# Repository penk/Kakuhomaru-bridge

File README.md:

# The Kakuhomaru Bridge Pickup for Electric Violins 

The Kakuhomaru (角宝丸) bridge is a piezoelectric pickup for electric violins, designed with a ‘one-sensor-per-string’ approach to capture each note with clarity and richness.

🔊 Listen to the open string sample here:

https://github.com/penk/Kakuhomaru-bridge/assets/61878/6f59927d-60b6-4801-80bd-5c879a68bae8

## Bill of materials  

Each Kakuhomaru bridge is composed of 4 main parts:

1. Piezoelectric rods and shielded cable (repurposed from guitar undersaddle pickups).
2. 3D printable case (available in both [low profile](./case/kakuhomaru-case-lowp.stl) and [high profile](./case/kakuhomaru-case-highp.stl)).
3. Custom printed circuit board (PCB) with castellated holes.
4. Semi-rigid electronically conductive foam (I'm using [this one](https://www.distrelec.de/en/conductive-foam-305x305x6mm-rnd-rnd-600-00067/p/30130228) which has a `30 ohm-meter (Ω·m)` volume resistance).

While some parts may require a few days of lead time, the assembly is straightforward and DIY-friendly once all components are in hand.

## Ordering the PCB

To get started with your PCB order, upload the [production file](./production/kakuhomaru-bridge-gerbers.zip) to your preferred PCB manufacturer, such as JLCPCB or PCBWay. Ensure you select `Castellated Holes`—essential for the functionality of our bridge pickup.

Here are the specifications I used for our prototype:

```
PCB Thickness: 1.6 mm 
PCB Color: Black
Remove Order Number: Yes
Castellated Holes: Yes
Edges: 2
```

For reference, ordering 10pcs from JLCPCB cost approximately $40. This should help you budget for your build.

## Assembly Instructions 

- Step 1: Attach the Piezoelectric Rods

    Carefully slice open the heat shrink tubing of the under-saddle pickup with a utility knife to retrieve the piezoelectric ceramics. Position the ceramics with the positive end towards the  E string (treble side) and the marked negative end towards the G string (bass side) . Fix them in place on the PCB using a tiny drop of CA glue at each end.

- Step 2: Solder the Shielded Cable & Insert the Conductive Foam

    Strip back a small portion of the shielded cable to expose the central positive wire. Solder this wire to the positive through-hole on the PCB. Attach the braided mesh, which acts as the negative wire, to the `GND` (ground) through-hole. Then, insert conductive foam into the eight castellated holes, using approximately 5mm cubic pieces.

- Step 3: Close the Protective Case  

    Place the PCB assmebly inside the [3D printed case](./case/) and secure it with two M2x10 screws. 

🔊 Test the bridge assembly with an amplifier once you complete the assembly to ensure proper functionality.

https://github.com/penk/Kakuhomaru-bridge/assets/61878/055f79b9-ad49-477b-b956-cf757c91dd27

## Setting up 

- Shielding: There's no need for copper shielding tape due to the PCB's integrated ground plane, which reduces interference.
- Grounding: Establish a grounding connection by connecting the shielded cable to the tuning pegs (if applicable) or directly to the string ends, depending on your violin setup.
- Bridge Shaping: Sand the bridge feet as you normally would and use a pencil to mark the grooves on the edge of the PCB for smooth string sliding.

## Further Customization

For those looking to tailor the bridge pickup to different sizes or heights, an [editable STEP file](./case/kakuhomaru-case.step) is available. This file allows you to make precise adjustments to the bridge to perfectly fit your instrument's unique specifications.

Additionally, if your setup requires a pickup for five or more strings, you can take advantage of the [fully editable KiCad project](./kicad). This project includes a [DXF outline](./case/kakuhomaru-PCB-outline.dxf), enabling you to design and customize your PCB to accommodate the specific needs of multi-string electric violins.

## Copyright and License
Copyright (c) 2024 Penk Chen. All rights reserved.

All files are licensed under MIT license, see the [LICENSE](LICENSE) for more information.

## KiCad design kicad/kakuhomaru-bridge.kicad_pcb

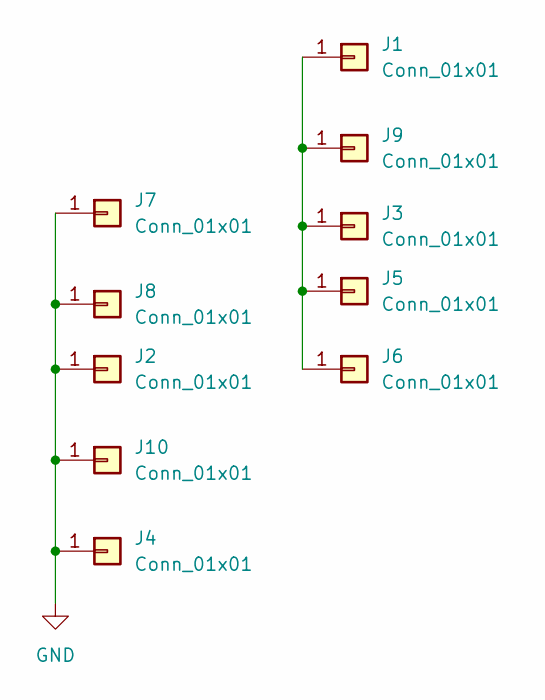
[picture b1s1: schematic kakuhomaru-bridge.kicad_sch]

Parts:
J1, J2, J3, J4, J5, J6, J7, J8, J9, J10: Conn_01x01; Pin_D1.0mm_L10.0mm

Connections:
GND: J2.1, J4.1, J7.1, J8.1, J10.1
unnamed: J1.1, J3.1, J5.1, J6.1, J9.1

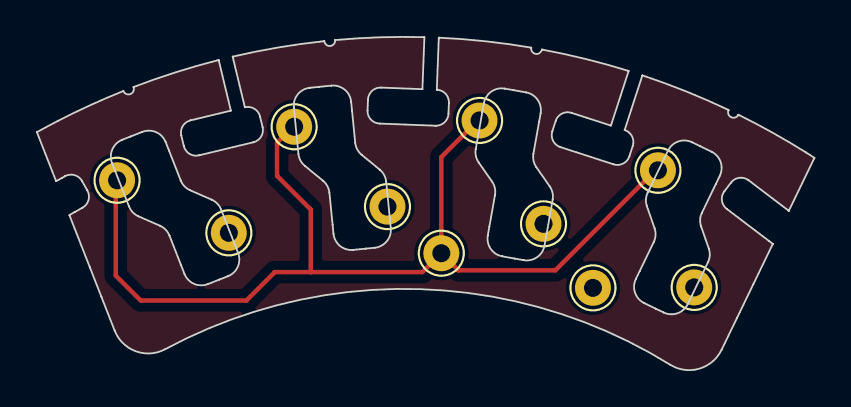
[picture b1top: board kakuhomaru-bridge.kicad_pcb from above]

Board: 2 copper layers, 43.2 x 18.5 mm, 10 parts (0 on the bottom side), 2 nets.

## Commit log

2024-04-22 Update README and add files
2024-04-22 Add customization screenshot
2024-05-12 Update PCB & case design
2024-05-22 Update case design
2024-05-22 Update reference pictures
2024-05-22 Update BOM reference picture
2024-05-22 Update cost
